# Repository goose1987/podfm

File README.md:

podfm
=====

fm transmitter adapter for ipod

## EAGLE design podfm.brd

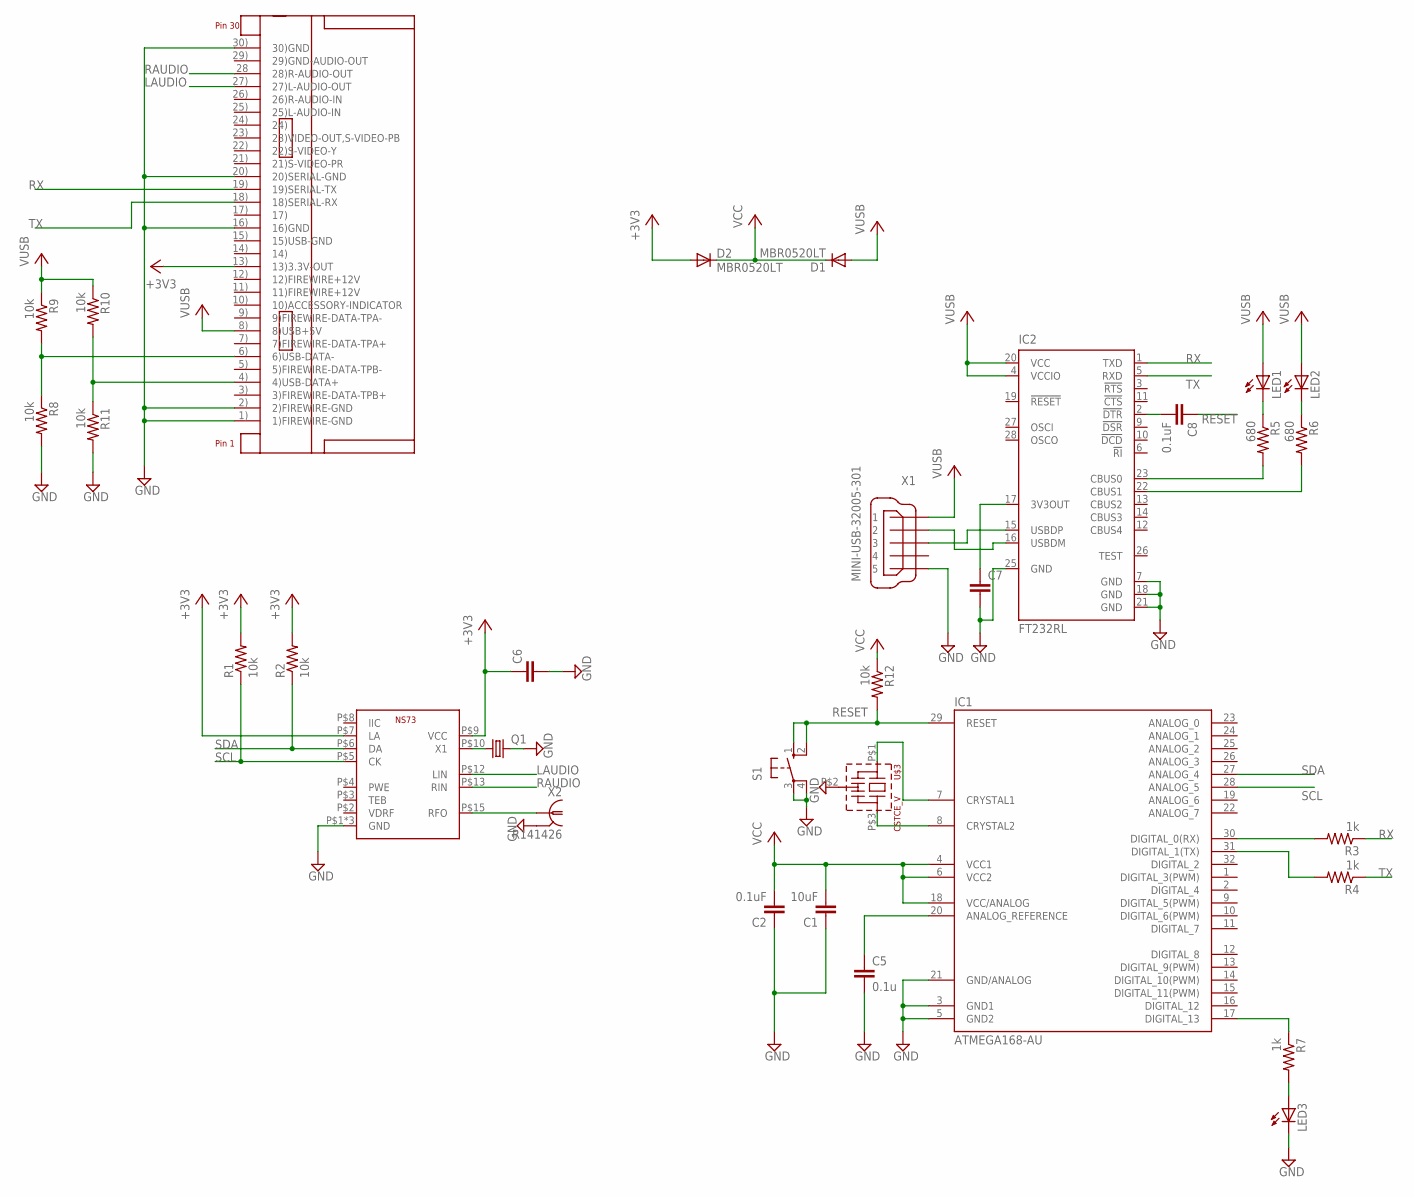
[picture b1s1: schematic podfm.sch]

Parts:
C1: 10uF; C1206
C2, C8: 0.1uF; C1206
C5: 0.1u; C1206
C6, C7: C-EUC1206; C1206
D1, D2: MBR0520LT; SOD123
IC1: ATMEGA168-AU; TQFP32-08
IC2: FT232RL; SSOP28
LED1, LED2, LED3: LED_ESML0603; LED_SML0603
Q1: CRYSTALTC26H; TC26H
R1, R2, R8, R9, R10, R11, R12: 10k; R1206
R3, R4, R7: 1k; R1206
R5, R6: 680; R0805
S1: 10-XX; B3F-10XX
U$1: NS73
U$2: IPOD-DOCK-CONNECTOR; IPOD_CONNECTOR
U$3: CSTCE_V
X1: MINI-USB-32005-301; 32005-301
X2: R141426

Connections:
+3V3: C6.1, D2.A, R1.2, R2.2, U$1.P$7 (LA), U$1.P$9 (VCC), U$2.13) (13)3.3V-OUT)
GND: C1.1, C2.1, C5.2, C6.2, C7.2, IC1.3 (GND1), IC1.5 (GND2), IC1.21 (GND/ANALOG), IC2.7 (GND), IC2.18 (GND), IC2.21 (GND), IC2.25 (GND), LED3.C, Q1.2, R8.2, R11.2, S1.3, S1.4 (P1), U$1.P$1 (GND), U$1.P$11 (GND), U$1.P$14 (GND), U$2.1) (1)FIREWIRE-GND), U$2.2) (2)FIREWIRE-GND), U$2.16) (16)GND), U$2.20) (20)SERIAL-GND), U$2.30) (30)GND), U$3.P$2 (VSS), X1.5, X1.M1 (5), X1.M2 (5), X1.M3 (5), X1.M4 (5), X2.2, X2.3 (2), X2.4 (2), X2.5 (2)
LAUDIO: U$1.P$12 (LIN), U$2.27) (27)L-AUDIO-OUT)
unnamed: U$1.P$15 (RFO), X2.1
unnamed: IC2.15 (USBDP), X1.3
unnamed: IC2.16 (USBDM), X1.2
unnamed: IC2.23 (CBUS0), R5.2
unnamed: IC2.22 (CBUS1), R6.2
unnamed: Q1.1, U$1.P$10 (X1)
unnamed: R10.2, R11.1, U$2.4) (4)USB-DATA+)
unnamed: R8.1, R9.2, U$2.6) (6)USB-DATA-)
unnamed: C7.1, IC2.17 (3V3OUT)
unnamed: IC1.30 (DIGITAL_0(RX)), R3.2
unnamed: IC1.31 (DIGITAL_1(TX)), R4.2
unnamed: C5.1, IC1.20 (ANALOG_REFERENCE)
unnamed: LED1.C, R5.1
unnamed: C8.2, IC2.2 (!DTR)
unnamed: LED2.C, R6.1
unnamed: IC1.17 (DIGITAL_13), R7.1
unnamed: LED3.A, R7.2
unnamed: IC1.7 (CRYSTAL1), U$3.P$1 (1)
unnamed: IC1.8 (CRYSTAL2), U$3.P$3 (3)
RAUDIO: U$1.P$13 (RIN), U$2.28 (28)R-AUDIO-OUT)
RESET: C8.1, IC1.29 (RESET), R12.2, S1.1 (S), S1.2 (S1)
RX: IC2.1 (TXD), R3.1, U$2.19) (19)SERIAL-TX)
SCL: IC1.28 (ANALOG_5), R1.1, U$1.P$5 (CK)
SDA: IC1.27 (ANALOG_4), R2.1, U$1.P$6 (DA)
TX: IC2.5 (RXD), R4.1, U$2.18) (18)SERIAL-RX)
VCC: C1.2, C2.2, D1.C, D2.C, IC1.4 (VCC1), IC1.6 (VCC2), IC1.18 (VCC/ANALOG), R12.1
VUSB: D1.A, IC2.4 (VCCIO), IC2.20 (VCC), LED1.A, LED2.A, R9.1, R10.1, U$2.8) (8)USB+5V), X1.1

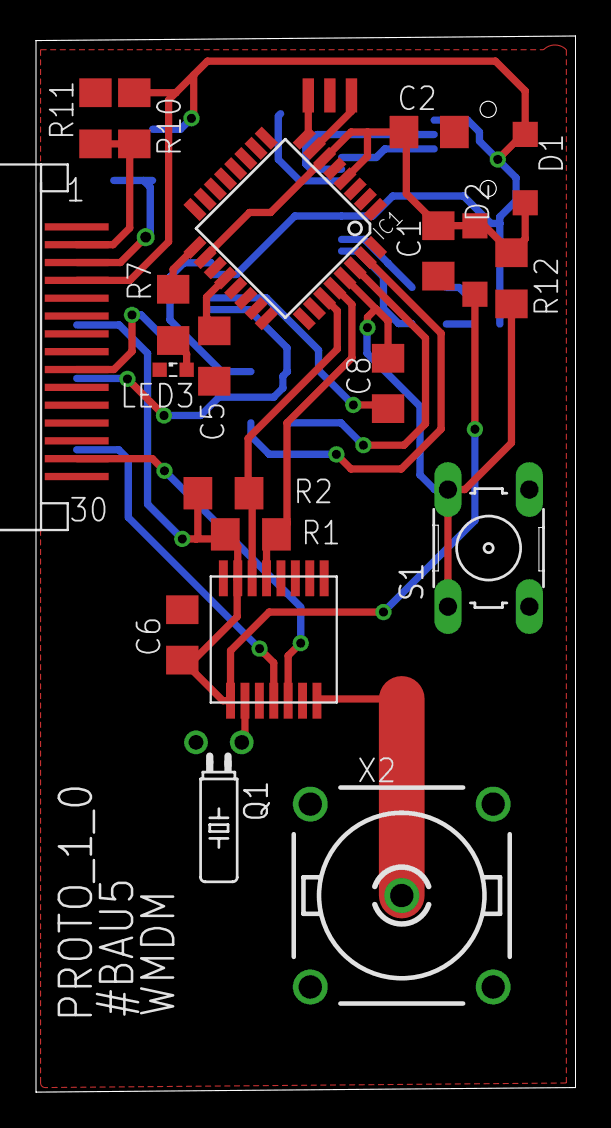
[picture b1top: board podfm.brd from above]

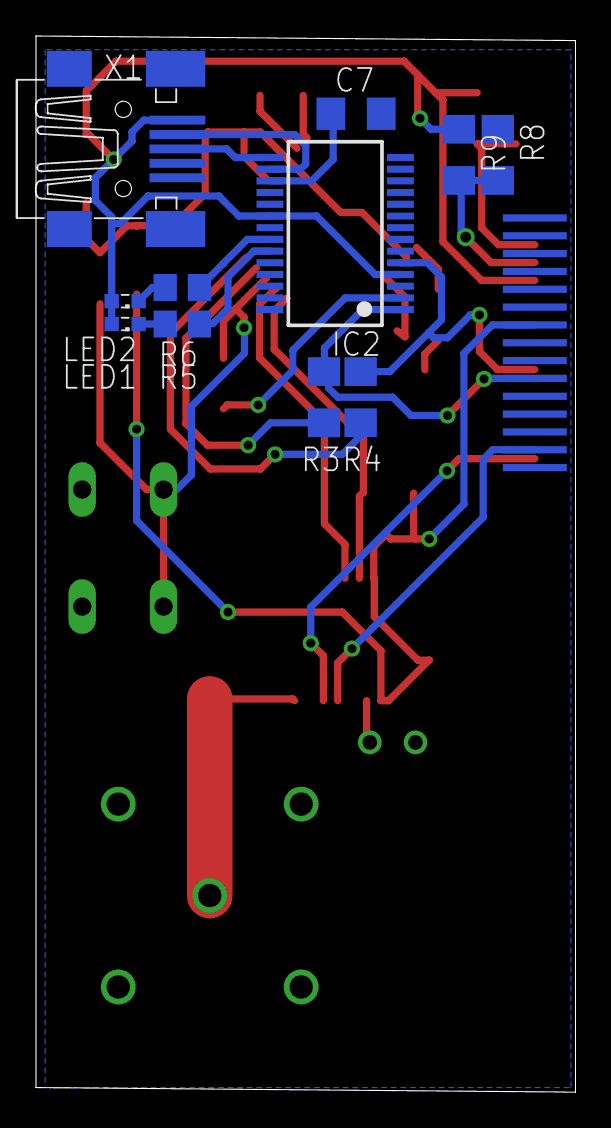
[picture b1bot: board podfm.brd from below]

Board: 2 copper layers, 30.0 x 58.7 mm, 32 parts (11 on the bottom side), 30 nets.

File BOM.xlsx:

Part | Value | Device | Package | Description | MF | MPN | OC_NEWARK | OC_DIGIKEY | QTY
C1 | 10uF | C-EUC1206 | C1206 | CAPACITOR, European symbol
C2 | 0.1uF | C-EUC1206 | C1206 | CAPACITOR, European symbol
C5 | 0.1u | C-EUC1206 | C1206 | CAPACITOR, European symbol
C6 |  | C-EUC1206 | C1206 | CAPACITOR, European symbol
C7 |  | C-EUC1206 | C1206 | CAPACITOR, European symbol
C8 | 0.1uF | C-EUC1206 | C1206 | CAPACITOR, European symbol
D1 | MBR0520LT | MBR0520LT | SOD123 | SCHOTTKY BARRIER RECTIFIER |  |  |  |  | 3
D2 | MBR0520LT | MBR0520LT | SOD123 | SCHOTTKY BARRIER RECTIFIER |  |  |  |  | 3
IC1 | ATMEGA168-AU | ATMEGA168-AU | TQFP32-08 |  |  |  |  | ATMEGA168-20AU-ND | 3
IC2 | FT232RL | FT232RL | SSOP28 | FTDI USB chip |  | FT232RL | 91K9918 | 768-1007-1-ND | 3
LED1 |  | LED_ESML0603 | LED_SML0603 | LED
LED2 |  | LED_ESML0603 | LED_SML0603 | LED
LED3 |  | LED_ESML0603 | LED_SML0603 | LED
Q1 |  | CRYSTALTC26H | TC26H | CRYSTAL |  |  | unknown
R1 | 10k | R-US_R1206 | R1206 | RESISTOR, American symbol
R2 | 10k | R-US_R1206 | R1206 | RESISTOR, American symbol
R3 | 1k | R-US_R1206 | R1206 | RESISTOR, American symbol
R4 | 1k | R-US_R1206 | R1206 | RESISTOR, American symbol
R5 | 680 | R-US_R0805 | R0805 | RESISTOR, American symbol
R6 | 680 | R-US_R0805 | R0805 | RESISTOR, American symbol
R7 | 1k | R-US_R1206 | R1206 | RESISTOR, American symbol
R8 | 10k | R-US_R1206 | R1206 | RESISTOR, American symbol
R9 | 10k | R-US_R1206 | R1206 | RESISTOR, American symbol
R12 | 10k | R-US_R1206 | R1206 | RESISTOR, American symbol
S1 |  | 10-XX | B3F-10XX | OMRON SWITCH |  | B3F-1000 | 36M3542
U$1 | NS73 | NS73 | NS73
U$2 | IPOD-DOCK-CONNECTOR | IPOD-DOCK-CONNECTOR | IPOD_CONNECTOR
U$3 | CSTCE_V | CSTCE_V | CSTCE_V |  |  |  |  | 490-1198-1-ND | 3
X1 | MINI-USB-32005-301 | MINI-USB-32005-301 | 32005-301 | MINI USB-B Conector |  |  | unknown
X2 | R141426 | R141426 | R141426 | BNC COAX CONNECTOR | FARNELL | R141426161 | 14J7919

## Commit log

2013-08-31 Hoang Pham 8/31/2013 initial board and schematic
2013-08-31 8/31/2013 Changed FTDI chip and atmega to bigger package for easier soldering. Add murata resonator
2013-09-01 8/31/2013 Fixed board dimension Moved silkscreen designator around for better visibility
2013-09-01 8/31/2013
    Created BOM
    renamed schematic and board file to be more
    consistent with project
2013-09-22 9/22/2013 fixed usb connection 1-VCC 2-data- 3-data+ 5-GND added resistor network for ipod iphone charging Signed-off-by: goose1987 <phamh1987@gmail.com>
